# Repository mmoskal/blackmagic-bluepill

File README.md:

# BMP firmware for Bluepill

This repo contains instructions needed to turn a [Bluepill board](https://stm32-base.org/boards/STM32F103C8T6-Blue-Pill.html)
into a [Black Magic Probe](https://github.com/blacksphere/blackmagic/wiki) debugger.
Black Magic Probe (BMP) runs a GDB server on the debug probe itself which allows for programming and debugging.
I've had best luck with connecting to targets under periodic sleep with BMP compared to openocd or pyocd.

The `dist/` folders contains binary builds of the BMP firmware.
The following changes have been applied, compared to `PROBE_HOST=stlink` default configuration:
* the SWDIO pin has been moved from PB14 to PB0
* the LED pin has been moved to PC13 (where the LED is on the Bluepill)
* the probe will assert target RESET signal on boot; this way the Bluepill reset button will reset both the probe and the target
* the Vref can be connected to PA0 without voltage divider
* disable Debug-in-STOP-mode registers - these cause trouble in my experience; it's possible this is now fixed in upstream bluepill

The file `dist/blackmagic_all.bin` needs to be flashed at `0x08000000` (beginning of flash).
This can be done using STLINK/V2 hardware and the following command:

```
openocd -c 'set FLASH_SIZE 0x20000' -f interface/stlink-v2.cfg -f target/stm32f1x.cfg -c 'program dist/blackmagic_all.bin verify reset exit 0x08000000'
```

You can also just run `./flash.sh` which does the same.

Many Bluepill boards announce 64KB, which is not enough for BMP.
The command above force-configures flash size to be 128KB
(the STM32F103C8 parts typically have 128KB but the upper half may be defective or not tested).
The command also verifies if the flash was written correctly - in case you get an error there, get a different Bluepill.

You can also use some STLINK GUI application, or any other methods for flashing.

## Getting Bluepill board

These are easily available on Amazon, Ebay, Aliexpress, etc. Search for `STM32F103C8T6`.
If you don't have a ST-LINK/V2 (clone), then get one as well (they often come together with Bluepills),
so you can re-program your Bluepill.

## Pinout

The basic SWD pinout follows.

|Pin |Function| Comments
|----|--------| ------------
|PB0 |SWDIO   | Required
|PA5 |SWCLK   | Required
|PB1 |RESET   | Optional - can be connected to NRST line of target
|PA10|SWO     | Optional - SWO is for logging, but is rarely used
|PA0 |Vref    | Optional - prints out target voltage on startup
|PC13|LED     | LED already connected on the Bluepill

The Bluepill will also act as a USB-Serial adapter (on the higher-numbered serial port).

|Pin |Function|
|----|--------|
|PA3 |RX      |
|PA2 |TX      |

If you want to use JTAG, here are the connections (but I have not tested these).

|Pin |Function|
|----|--------|
|PB0 |TMS     |
|PA7 |TDI     |
|PA6 |TDO     |
|PA5 |TCK     |

## Hack-Connect XS cable

You can solder a Cortex-M debug cable (10 pin 0.05 inch pitch IDC cable; 8 or 6 pin will work as well)
to a Blue Pill directly and use [Hack-Connect-XS](https://arcade.makecode.com/hardware/dbg).

First cut one end of the cable (see picture above to determine which one) and split the first 5 wires.
Wire number 1 is red.
Strip isolation from the 5 wires, and cut away the remaining 5 wires.
Keep the GND and VCC wires about 15mm longer.

Next, connect a female jumper cable to VCC wire - you can either twist them together or solder (don't forget to isolate after connecting!).
You can later connect it to VCC pin of the Blue Pill (on its debug header) to power the target when needed.
Then solder the remaining wires to Blue Pill as indicated in the picture above.
Wrap the whole thing in electrical tape for cable strain relief.

Next, cut 6 pins from a 0.05 inch dual row male header.
You may want to cut 8 pins and remove the excessive pins (the plastic often breaks at the pin boundary).
Remove one pin, as indicated.
Finally, remove excessive plastic.

Now, insert the header into the connector, aligning the left side with the red wire.
There should be 3 pins on the outer edge and 2 on the inner.
You can test your cable now, before gluing - the header will likely stay in PCB when you pull out the cable, which is why we’re glueing.
After testing, pull out the header out slightly (around 1mm), put a drop of glue in the gap, and then press the connector back in.
Leave it to dry for a few minutes (it will stick to PCB if it doesn’t dry!).

## Bluepill-BMP shield

If you don't feel like breadboarding the pinout above,
the `eagle/` folder contains design files for a shield with 2x5pin 50mil Cortex debug connector,
a switch for powering the target, and a reset button for the target.
The Gerber files are also included.

It also lets you optionally use pin 5 of the Cortex debug connector as RESET line,
so you can use Hack-Connect-XS without any cable slicing - once you set the jumper into HC-XS position,
just use a regular 2x5pin IDC cable, with
[the male header inserted on target side](https://arcade.makecode.com/hardware/dbg#target-end).

(This shield is why I do not use the `swlink` BMP target)

Note that the `RX`/`TX` pins on the shield are meant to solder a header pointing away from the Bluepill
(see picture below).
You can connect an external serial port to it, and see it as one of the BMP serial ports.

## License

The Black Magic Probe firmware https://github.com/blacksphere/blackmagic
is licensed under GPL v3.
See https://github.com/mmoskal/blackmagic/tree/bluepill for the
[patches applied](https://github.com/blackmagic-debug/blackmagic/compare/main...mmoskal:blackmagic:bluepill);
to build use `make PROBE_HOST=stlink BLUEPILL=1`

The Eagle files contain parts based on ones from 
* SparkFun Eagle Libraries https://github.com/sparkfun/SparkFun-Eagle-Libraries licensed under CC-SA-4.0
* Adafruit Eagle Libraries https://github.com/adafruit/Adafruit-Eagle-Library

Any new content is licensed under MIT.

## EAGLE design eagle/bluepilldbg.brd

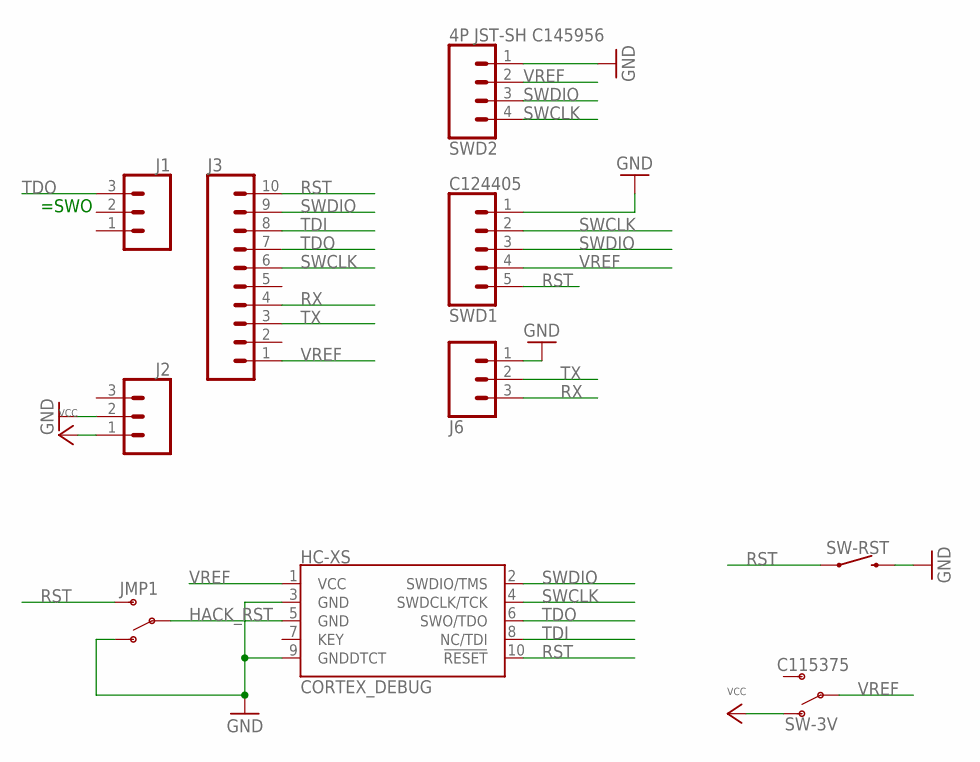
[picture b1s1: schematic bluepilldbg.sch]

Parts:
HC-XS: CORTEX_DEBUG; CON5X2_1.27
J1, J2, J6: CONN_031X03_NO_SILK; 1X03_NO_SILK
J3: CONN_10NO_SILK_PTH_FEMALE; 1X10_NO_SILK
JMP1: SWITCH-SPDT-HD; 1X03_NO_SILK
SW-3V: C115375; SWITCH_DPDT_SMD_AYZ0202
SW-RST: C255816; TACTILE_SWITCH_SMD_6.0X3.5MM
SWD1: C124405; 1X05_SMALLHOLE
SWD2: 4P JST-SH C145956; JST04_1MM_RA

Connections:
GND: HC-XS.3 (GND), HC-XS.9 (GNDDTCT), J2.2, J6.1, JMP1.1 (O), SW-RST.2, SWD1.1, SWD2.1
HACK_RST: HC-XS.5 (GND), JMP1.2
RST: HC-XS.10 (!RESET), J3.10, JMP1.3 (S), SW-RST.1, SWD1.5
RX: J3.4, J6.3
SWCLK: HC-XS.4 (SWDCLK/TCK), J3.6, SWD1.2, SWD2.4
SWDIO: HC-XS.2 (SWDIO/TMS), J3.9, SWD1.3, SWD2.3
TDI: HC-XS.8 (NC/TDI), J3.8
TDO: HC-XS.6 (SWO/TDO), J1.3, J3.7
TX: J3.3, J6.2
VCC: J2.1, SW-3V.1 (O), SW-3V.4 (O)
VREF: HC-XS.1 (VCC), J3.1, SW-3V.2, SW-3V.5, SWD1.4, SWD2.2

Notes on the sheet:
=SWO

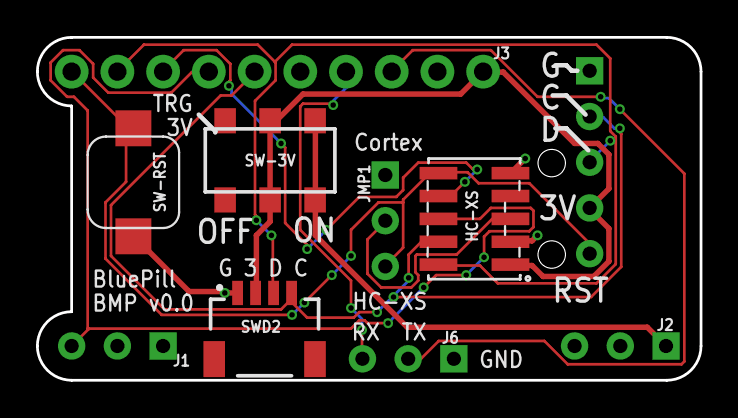
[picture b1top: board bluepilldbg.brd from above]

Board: 2 copper layers, 36.9 x 19.0 mm, 10 parts (0 on the bottom side), 11 nets.

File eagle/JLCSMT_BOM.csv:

Comment,Designator,Footprint,LCSC Part#
"SWITCH-SPDT-SMD-AYZ0202 C115375","SW-3V","SW-TH","C115375"
"MOMENTARY-SWITCH-SPST-SMD-6.0X3.5MM C255816","SW-RST","SW-SMD","C255816"
"CONN_05SMALLHOLE C124405","SWD1","HDR-TH_5P-P2.54_220R-1_+_5P","C124405"
"CONN_04SMD2 4P JST-SH C145956","SWD2","SMD_P=1mm","C145956"

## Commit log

2021-02-22 Initial version of the Eagle files
2021-02-24 smaller pcb
2021-02-24 Nicer schematics; place part names
2021-03-11 Re-order JST-SH debug connector to match QWIIC
2021-03-11 Production files
2021-03-12 Add more docs
2021-03-12 Build https://github.com/mmoskal/blackmagic/commit/b1701a80cd2c759a41499e5864edf53a006c4a28
2021-03-12 More notes on flashing
2021-03-12 Add header image
2021-03-17 Binary build for https://github.com/mmoskal/blackmagic/commit/286acbb9457e6ece550b458482572b8895c93f42
2021-03-20 add flash.sh
2021-03-26 Link more to HC-XS
2021-03-26 Add shield image
2021-03-26 Build https://github.com/mmoskal/blackmagic/commit/3a0df369cda3918883ba007300bebb710e0ed5fa
2021-03-28 Add info on getting Bluepill
2021-09-21 add part numbers and BOM
2022-04-06 add soldering info
2022-06-12 clarify
2022-06-22 Build https://github.com/mmoskal/blackmagic/commit/812a2233b978a04c69a5d581f729d46578f7a303
2022-06-22 specify CPUTAPID explicitly
2022-07-13 add inline cable guide
2022-07-13 add flashing script for BMP
2022-11-29 fix comparison link
2022-11-29 there is one more change

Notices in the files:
parts and their libraries:
SparkFun-Connectors: Licensing: Creative Commons ShareAlike 4.0 International - https://creativecommons.org/licenses/by-sa/4.0
